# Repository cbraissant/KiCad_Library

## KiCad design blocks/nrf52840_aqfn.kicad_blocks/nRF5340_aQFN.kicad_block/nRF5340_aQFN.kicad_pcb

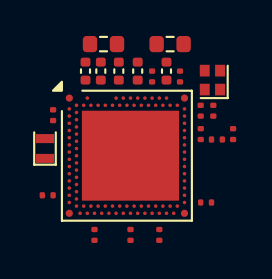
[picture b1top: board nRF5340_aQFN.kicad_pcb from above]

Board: 2 copper layers, 23 parts (0 on the bottom side), 14 nets, no tracks yet.

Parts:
C1: 0.7pF; C_0201_0603Metric
C2, C3, C5, C7, C16: 1.0uF; C_0402_1005Metric
C4: 2.2nF; C_0201_0603Metric
C6, C8, C9, C10, C11, C12, C13, C14, C15: 100nF; C_0201_0603Metric
C21: C_0201_0603Metric
L1: 10uH; L_0201_0603Metric
L2, L3: 10uH; L_0603_1608Metric
U1: Nordic nRF5340; Nordic_AQFN-94-1EP_7x7mm_P0.4mm
X1: 32MHz; Crystal_SMD_1612-4Pin_1.6x1.2mm
X2: 32.768kHz; Crystal_SMD_1610-2Pin_1.6x1.0mm

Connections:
+3V3: C2.1, C8.1, C9.1, C10.1, C11.1, C12.1, C13.1, C14.1, C15.1, C16.1, U1.A19 (VDD), U1.AC1 (VDD), U1.AG1 (VDD), U1.AJ31 (VDD), U1.AL3 (VDD), U1.AL7 (VDD), U1.AL11 (VDD), U1.AL17 (VDD), U1.AL25 (VDD), U1.B8 (VDD), U1.B28 (VDD), U1.C1 (VDD), U1.E1 (VDDH), U1.E31 (VDD), U1.L1 (VDD), U1.N31 (VDD), U1.U1 (VDD)
GND: C1.2, C2.2, C3.2, C4.2, C5.2, C6.2, C7.2, C8.2, C9.2, C10.2, C11.2, C12.2, C13.2, C14.2, C15.2, C16.2, C21.2, U1.A5 (VBUS), U1.A25 (NC/GND), U1.B12 (NC/GND), U1.B26 (NC/GND), U1.EP (GND), U1.G1 (NC/GND), U1.H2 (NC/GND), U1.J31 (NC/GND), X1.2 (G), X1.4 (G)
unnamed: C21.1, L1.1
unnamed: C1.1, L1.2, U1.L31 (ANT)
unnamed: L2.1, U1.A21 (DCC)
unnamed: L3.1, U1.B10 (DCCD)
unnamed: C7.1, U1.A13 (DECA)
unnamed: C5.1, L3.2, U1.A15 (DECD)
unnamed: C6.1, U1.A23 (DECN)
unnamed: C3.1, C4.1, L2.2, U1.A27 (DECR), U1.G31 (DECRF)
unnamed: U1.C31 (XC1), X1.1
unnamed: U1.B30 (XC2), X1.3
unnamed: U1.N1 (P0.00/XL1), X2.2
unnamed: U1.R1 (P0.01/XL2), X2.1

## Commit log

2025-12-16 add Hirose BM23 connectors
2025-12-16 update components
2026-03-18 update footprint and 3D models
2026-05-19 update symbols
2026-06-09 update footprint and symbols
